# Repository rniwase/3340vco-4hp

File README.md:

# 3340VCO
An 4HP Eurorack VCO module using Coolaudio V3340 (CEM3340 second-source).

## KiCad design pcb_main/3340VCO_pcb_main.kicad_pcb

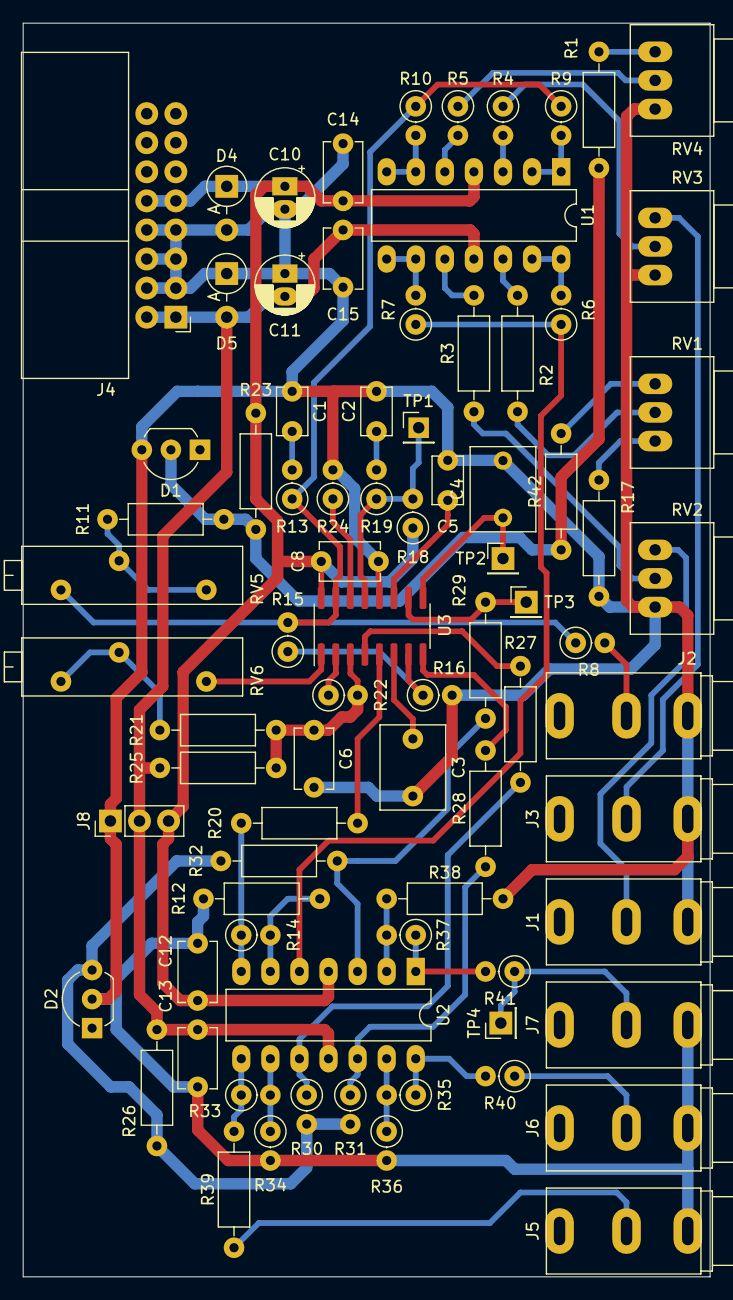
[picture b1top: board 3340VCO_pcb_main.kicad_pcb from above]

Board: 2 copper layers, 60.0 x 109.5 mm, 80 parts (0 on the bottom side), 56 nets.

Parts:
C1, C2: 10n; C_Rect_L4.0mm_W2.5mm_P2.50mm
C3, C4: 0.1μ; C_Rect_L7.2mm_W5.5mm_P5.00mm_FKS2_FKP2_MKS2_MKP2
C5: 1n; C_Rect_L4.0mm_W2.5mm_P2.50mm
C6, C8: 2.2μ; C_Disc_D5.1mm_W3.2mm_P5.00mm
C10, C11: 22μ; CP_Radial_D5.0mm_P2.00mm
C12, C13, C14, C15: 10μ; C_Disc_D5.1mm_W3.2mm_P5.00mm
D1, D2: LM336Z-5.0; TO-92_Inline_Wide
D4, D5: 1N4007; D_DO-41_SOD81_P3.81mm_Vertical_AnodeUp
J1, J2, J3, J5, J6, J7: MJ-352
J4: POWER_IN; IDC-Header_2x08_P2.54mm_Horizontal
J8: EXT_POW; PinHeader_1x03_P2.54mm_Vertical
R1: 150k; R_Axial_DIN0207_L6.3mm_D2.5mm_P10.16mm_Horizontal
R2, R3, R12: 100k; R_Axial_DIN0207_L6.3mm_D2.5mm_P10.16mm_Horizontal
R4, R5, R6, R7, R8, R9, R10, R14: 100k; R_Axial_DIN0207_L6.3mm_D2.5mm_P2.54mm_Vertical
R11: 82k; R_Axial_DIN0207_L6.3mm_D2.5mm_P10.16mm_Horizontal
R13: 470; R_Axial_DIN0207_L6.3mm_D2.5mm_P2.54mm_Vertical
R15, R18: 1.5M; R_Axial_DIN0207_L6.3mm_D2.5mm_P2.54mm_Vertical
R16: 10k; R_Axial_DIN0207_L6.3mm_D2.5mm_P2.54mm_Vertical
R17: 1.5k; R_Axial_DIN0207_L6.3mm_D2.5mm_P10.16mm_Horizontal
R19: 560; R_Axial_DIN0207_L6.3mm_D2.5mm_P2.54mm_Vertical
R20, R32: 10k; R_Axial_DIN0207_L6.3mm_D2.5mm_P10.16mm_Horizontal
R21: 24k; R_Axial_DIN0207_L6.3mm_D2.5mm_P10.16mm_Horizontal
R22: 5.6k; R_Axial_DIN0207_L6.3mm_D2.5mm_P2.54mm_Vertical
R23, R26: 1k; R_Axial_DIN0207_L6.3mm_D2.5mm_P10.16mm_Horizontal
R24: 1.8k; R_Axial_DIN0207_L6.3mm_D2.5mm_P2.54mm_Vertical
R25: 510; R_Axial_DIN0207_L6.3mm_D2.5mm_P10.16mm_Horizontal
R27: 12k; R_Axial_DIN0207_L6.3mm_D2.5mm_P10.16mm_Horizontal
R28, R42: 27k; R_Axial_DIN0207_L6.3mm_D2.5mm_P10.16mm_Horizontal
R29: 3.9k; R_Axial_DIN0207_L6.3mm_D2.5mm_P10.16mm_Horizontal
R30: 20k; R_Axial_DIN0207_L6.3mm_D2.5mm_P2.54mm_Vertical
R31: 33k; R_Axial_DIN0207_L6.3mm_D2.5mm_P2.54mm_Vertical
R33: 0; R_Axial_DIN0207_L6.3mm_D2.5mm_P2.54mm_Vertical
R34: DNP; R_Axial_DIN0207_L6.3mm_D2.5mm_P2.54mm_Vertical
R35: 27k; R_Axial_DIN0207_L6.3mm_D2.5mm_P2.54mm_Vertical
R36: 22k; R_Axial_DIN0207_L6.3mm_D2.5mm_P2.54mm_Vertical
R37: 15k; R_Axial_DIN0207_L6.3mm_D2.5mm_P2.54mm_Vertical
R38: 5.6k; R_Axial_DIN0207_L6.3mm_D2.5mm_P10.16mm_Horizontal
R39: 100; R_Axial_DIN0207_L6.3mm_D2.5mm_P10.16mm_Horizontal
R40, R41: 100; R_Axial_DIN0207_L6.3mm_D2.5mm_P2.54mm_Vertical
RV1, RV2, RV3, RV4: 100k; Potentiometer_Alps_RK097_Single_Horizontal
RV5: 50k; Potentiometer_Bourns_3006P_Horizontal
RV6: 10k; Potentiometer_Bourns_3006P_Horizontal
TP1: VLFI; PinHeader_1x01_P2.54mm_Vertical
TP2: VSSI; PinHeader_1x01_P2.54mm_Vertical
TP3: VTO; PinHeader_1x01_P2.54mm_Vertical
TP4: TRIOUT; PinHeader_1x01_P2.54mm_Vertical
U1, U2: NJM074; DIP-14_W7.62mm_LongPads
U3: V3340M; SOIC-16_3.9x9.9mm_P1.27mm

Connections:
+5V: D1.2, R1.1, R11.2, R23.2, R42.1
+12V: C8.2, C10.1, C12.1, C14.1, D4.1, J4.9, J4.10, J8.3, R18.1, R23.1, U1.4, U2.4, U3.16
-5V: D2.3, R26.1, R30.2, R31.2, R32.2
-12V: C11.2, C13.1, C15.1, D5.2, J4.1, J4.2, J8.2, R25.2, R26.2, U1.11, U2.11
GND: C1.2, C2.2, C3.2, C4.2, C5.2, C6.2, C8.1, C10.2, C11.1, C12.2, C13.2, C14.2, C15.2, D1.3, D2.2, D4.2, D5.1, J1.S, J2.S, J3.S, J4.3, J4.4, J4.5, J4.6, J4.7, J4.8, J5.S, J6.S, J7.S, J8.1, R12.2, R16.2, R17.2, R24.2, R34.2, R36.2, R38.2, RV2.1, RV3.1, RV4.1, U3.12
unnamed: C1.1, R13.2
unnamed: C2.1, R19.2
unnamed: C3.1, U3.6
unnamed: C4.1, TP2.1, U3.9
unnamed: C5.1, U3.11
unnamed: J1.T, RV2.3
unnamed: J2.T, R8.2
unnamed: J3.T, RV3.3
unnamed: J5.T, R39.1
unnamed: J6.T, R40.1
unnamed: J7.T, R41.1, TP4.1
unnamed: R1.2, RV4.3
unnamed: R2.1, U1.12
unnamed: R2.2, RV1.2
unnamed: R3.1, U1.10
unnamed: R3.2, RV2.2
unnamed: R4.1, RV3.2
unnamed: R4.2, U1.3
unnamed: R5.1, RV4.2
unnamed: R5.2, U1.5
unnamed: R6.1, R7.1, U2.5
unnamed: R6.2, U1.13, U1.14
unnamed: R7.2, U1.8, U1.9
unnamed: R9.2, U1.1, U1.2
unnamed: R8.1, R9.1, R10.1, R13.1, R15.2, RV5.3, U3.15
unnamed: R10.2, U1.6, U1.7
unnamed: R11.1, RV5.1, RV5.2
unnamed: R12.1, R14.2, U2.6
unnamed: R14.1, R20.2, U2.7
unnamed: R15.1, R16.1, U3.7
unnamed: R17.1, RV1.1
unnamed: R18.2, R19.1, TP1.1, U3.13
unnamed: R20.1, U3.5
unnamed: R21.1, RV6.2, RV6.3
unnamed: R22.1, U3.2
unnamed: R24.1, U3.14
unnamed: R27.1, R30.1, U2.10
unnamed: R27.2, U3.4
unnamed: R28.1, R31.1, U2.12
unnamed: R28.2, U3.8
unnamed: R29.1, R32.1, U2.3
unnamed: R29.2, TP3.1, U3.10
unnamed: R33.1, R39.2, U2.8
unnamed: R33.2, R34.1, U2.9
unnamed: R35.1, R40.2, U2.14
unnamed: R35.2, R36.1, U2.13
unnamed: R37.1, R41.2, U2.1
unnamed: R37.2, R38.1, U2.2
unnamed: R42.2, RV1.3
unnamed: RV6.1, U3.1
VEE: C6.1, R21.2, R22.2, R25.1, U3.3

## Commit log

2020-05-11 pcb_main modify height: 114.5->109.5mm, optimize pad/drill diameter
2020-05-11 adjust vertical hole position
2020-05-12 flip RV5 pin assign, add power source protection diode
2020-05-13 update schematic
2020-05-14 redesign pcb_main for double-side
2020-05-14 fix typo
2020-05-14 update draft cad data
2020-05-14 tweak pcb_main, adjust frontpanel horizontal position
2020-05-15 output gerber
2020-05-16 update flatcam project, export and modify G-code
2020-05-22 place F.Silk
2020-06-15 update TODO list
2020-08-15 replace reference Diode: 1N5231B to LM336Z-5.0, update schematic and pcb
2020-08-16 modify frontpanel g-code
2020-08-16 regenerate gerber, g-code
2020-08-16 add g-code
2020-08-17 fix g-code
2020-08-24 add photo
2020-12-11 add .gitattributes
2022-08-26 migrate to KiCAD 6.0
